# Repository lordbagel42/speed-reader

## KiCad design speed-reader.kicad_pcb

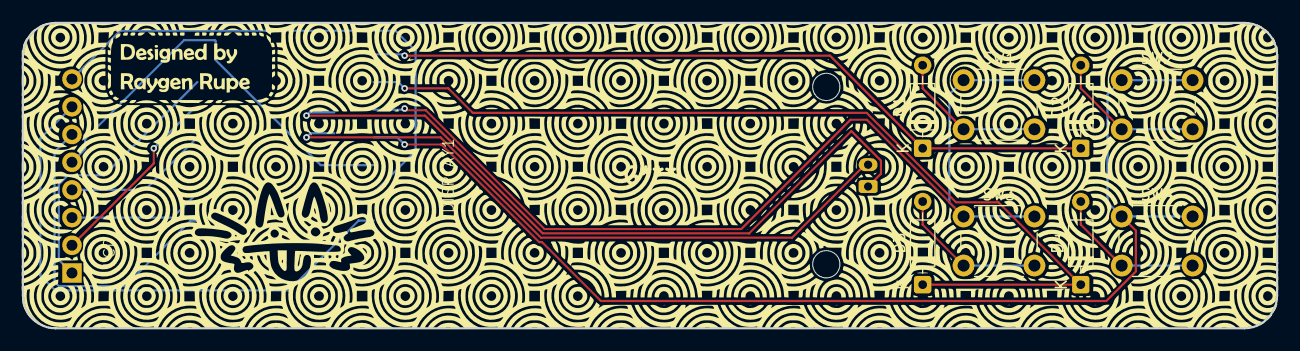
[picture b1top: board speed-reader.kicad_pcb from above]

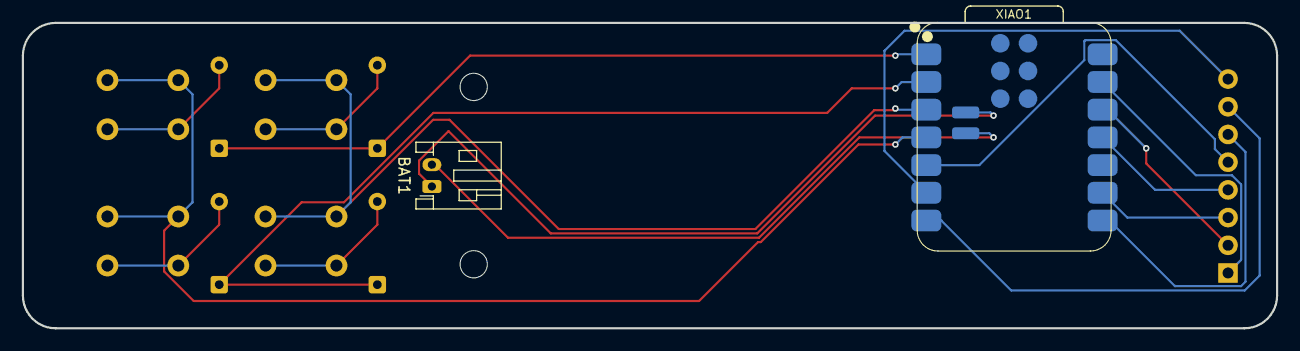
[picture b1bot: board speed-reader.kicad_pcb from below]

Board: 2 copper layers, 115.0 x 28.0 mm, 11 parts (2 on the bottom side), 18 nets.

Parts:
BAT1: Conn_01x02_Socket; JST_PH_S2B-PH-K_1x02_P2.00mm_Horizontal
D1, D2, D3, D4: 1N4148WT; D_DO-35_SOD27_P7.62mm_Horizontal
DISPLAY1: display
SW1, SW2, SW3, SW4: SW_Push; SW_PUSH_6mm
XIAO1: XIAO-ESP32-C3-SMD

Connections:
/BL: DISPLAY1.BL, XIAO1.6 (GPIO7_D5_SCL)
/COL0: SW1.1, SW3.1, XIAO1.3 (GPIO4_A2_D2)
/COL1: SW2.1, SW4.1, XIAO1.4 (GPIO5_A3_D3)
/CS: DISPLAY1.CS, XIAO1.7 (GPIO21_D6_TX)
/DC: DISPLAY1.DC, XIAO1.8 (GPIO20_D7_RX)
/ROW0: D1.1 (K), D2.1 (K), XIAO1.1 (GPIO2_A0_D0)
/ROW1: D3.1 (K), D4.1 (K), XIAO1.2 (GPIO3_A1_D1)
/RST: DISPLAY1.RST, XIAO1.5 (GPIO6_D4_SDA)
/SCL: DISPLAY1.SCL, XIAO1.9 (GPIO8_D8_SCK)
/SDA: DISPLAY1.SDA, XIAO1.11 (GPIO10_D10_MOSI)
GND: DISPLAY1.GND, XIAO1.13 (GND)
unnamed: BAT1.1, XIAO1.22 (GND)
unnamed: BAT1.2, XIAO1.21 (BAT)
unnamed: D1.2 (A), SW1.2
unnamed: D2.2 (A), SW2.2
unnamed: D3.2 (A), SW3.2
unnamed: D4.2 (A), SW4.2
VCC: DISPLAY1.VCC, XIAO1.12 (3V3)

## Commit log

2026-06-18 upload the doohickey
2026-06-18 journal.md, production files, readme
2026-06-18 journalllllllllllllllllllll
2026-06-18 oop forgot battery connectors
2026-06-18 name
2026-06-18 credits!
